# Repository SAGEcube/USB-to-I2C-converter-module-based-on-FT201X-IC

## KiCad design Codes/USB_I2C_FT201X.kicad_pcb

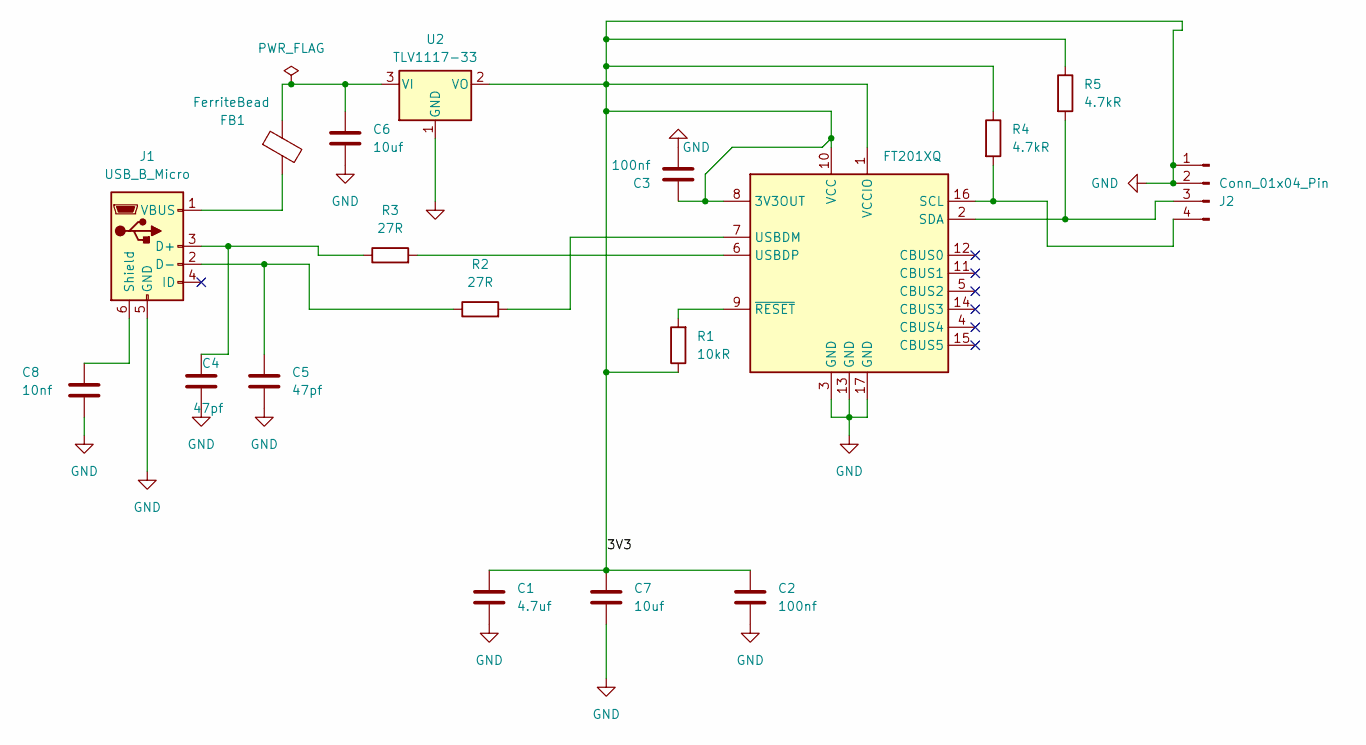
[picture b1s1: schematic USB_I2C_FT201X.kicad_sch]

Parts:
C1: 4.7uf; C_0603_1608Metric
C2, C3: 100nf; C_0603_1608Metric
C4, C5: 47pf; C_0603_1608Metric
C6, C7: 10uf; C_0603_1608Metric
C8: 10nf; C_0603_1608Metric
FB1: FerriteBead; L_0603_1608Metric
J1: USB_B_Micro; USB_Micro-B_Amphenol_10103594-0001LF_Horizontal
J2: Conn_01x04_Pin; PinHeader_1x04_P2.54mm_Vertical
R1: 10kR; R_0603_1608Metric
R2, R3: 27R; R_0603_1608Metric
R4, R5: 4.7kR; R_0603_1608Metric
U1: FT201XQ; QFN-16-1EP_3x3mm_P0.5mm_EP1.7x1.7mm
U2: TLV1117-33; SOT-223

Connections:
GND: C1.1, C1.2, C2.1, C2.2, C3.1, C3.2, C4.2, C5.2, C6.2, C7.1, C7.2, C8.2, J1.5 (GND), J2.1, J2.2, R1.1, R4.1, R5.1, U1.1 (VCCIO), U1.3 (GND), U1.8 (3V3OUT), U1.10 (VCC), U1.13 (GND), U1.17 (GND), U2.1 (GND), U2.2 (VO)
unnamed: C4.1, J1.3 (D+), R3.1
unnamed: C5.1, J1.2 (D-), R2.1
unnamed: C8.1, J1.6 (Shield)
unnamed: FB1.2, J1.1 (VBUS)
unnamed: J2.3, R5.2, U1.2 (SDA)
unnamed: J2.4, R4.2, U1.16 (SCL)
unnamed: R2.2, U1.7 (USBDM)
unnamed: R3.2, U1.6 (USBDP)
unnamed: R1.2, U1.9 (~RESET)
unnamed: C6.1, FB1.1, U2.3 (VI)

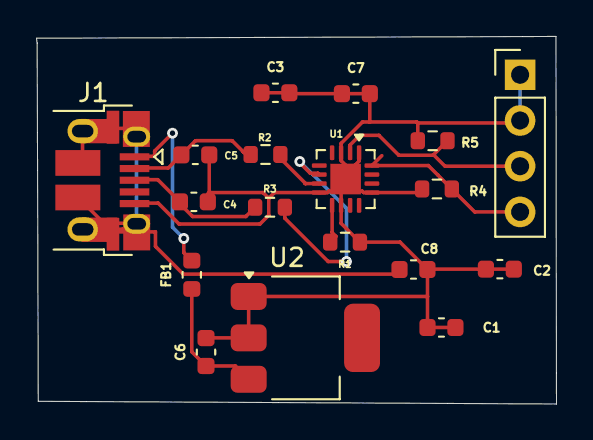
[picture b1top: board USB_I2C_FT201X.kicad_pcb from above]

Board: 2 copper layers, 28.9 x 20.4 mm, 18 parts (0 on the bottom side), 11 nets.
